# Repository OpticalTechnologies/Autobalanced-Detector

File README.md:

# Autobalanced-Detector
Full KiCAD design and production files of a self designed autobalanced detector for SRS microscopy. 

The autobalanced detector consists of three parts: 
1. Two of the same detectors (SRSDetV5_24V) to detect the signal and reference beam.
2. The autobalancer module.
3. The PID controller, which is designed as a seperate PCB controlled by an MCU. The MCU also controlls logic circuitry on the autobalancer module.

The SRSDetV5 is optimized for use with a 20MHz modulation frequency and incorperates several filters to supress the repetition rate of a 40MHz pulsed laser and its harmonics. 

Firmware for the PID MCU and instructions on how to upload the firmware to the MCU will follow.

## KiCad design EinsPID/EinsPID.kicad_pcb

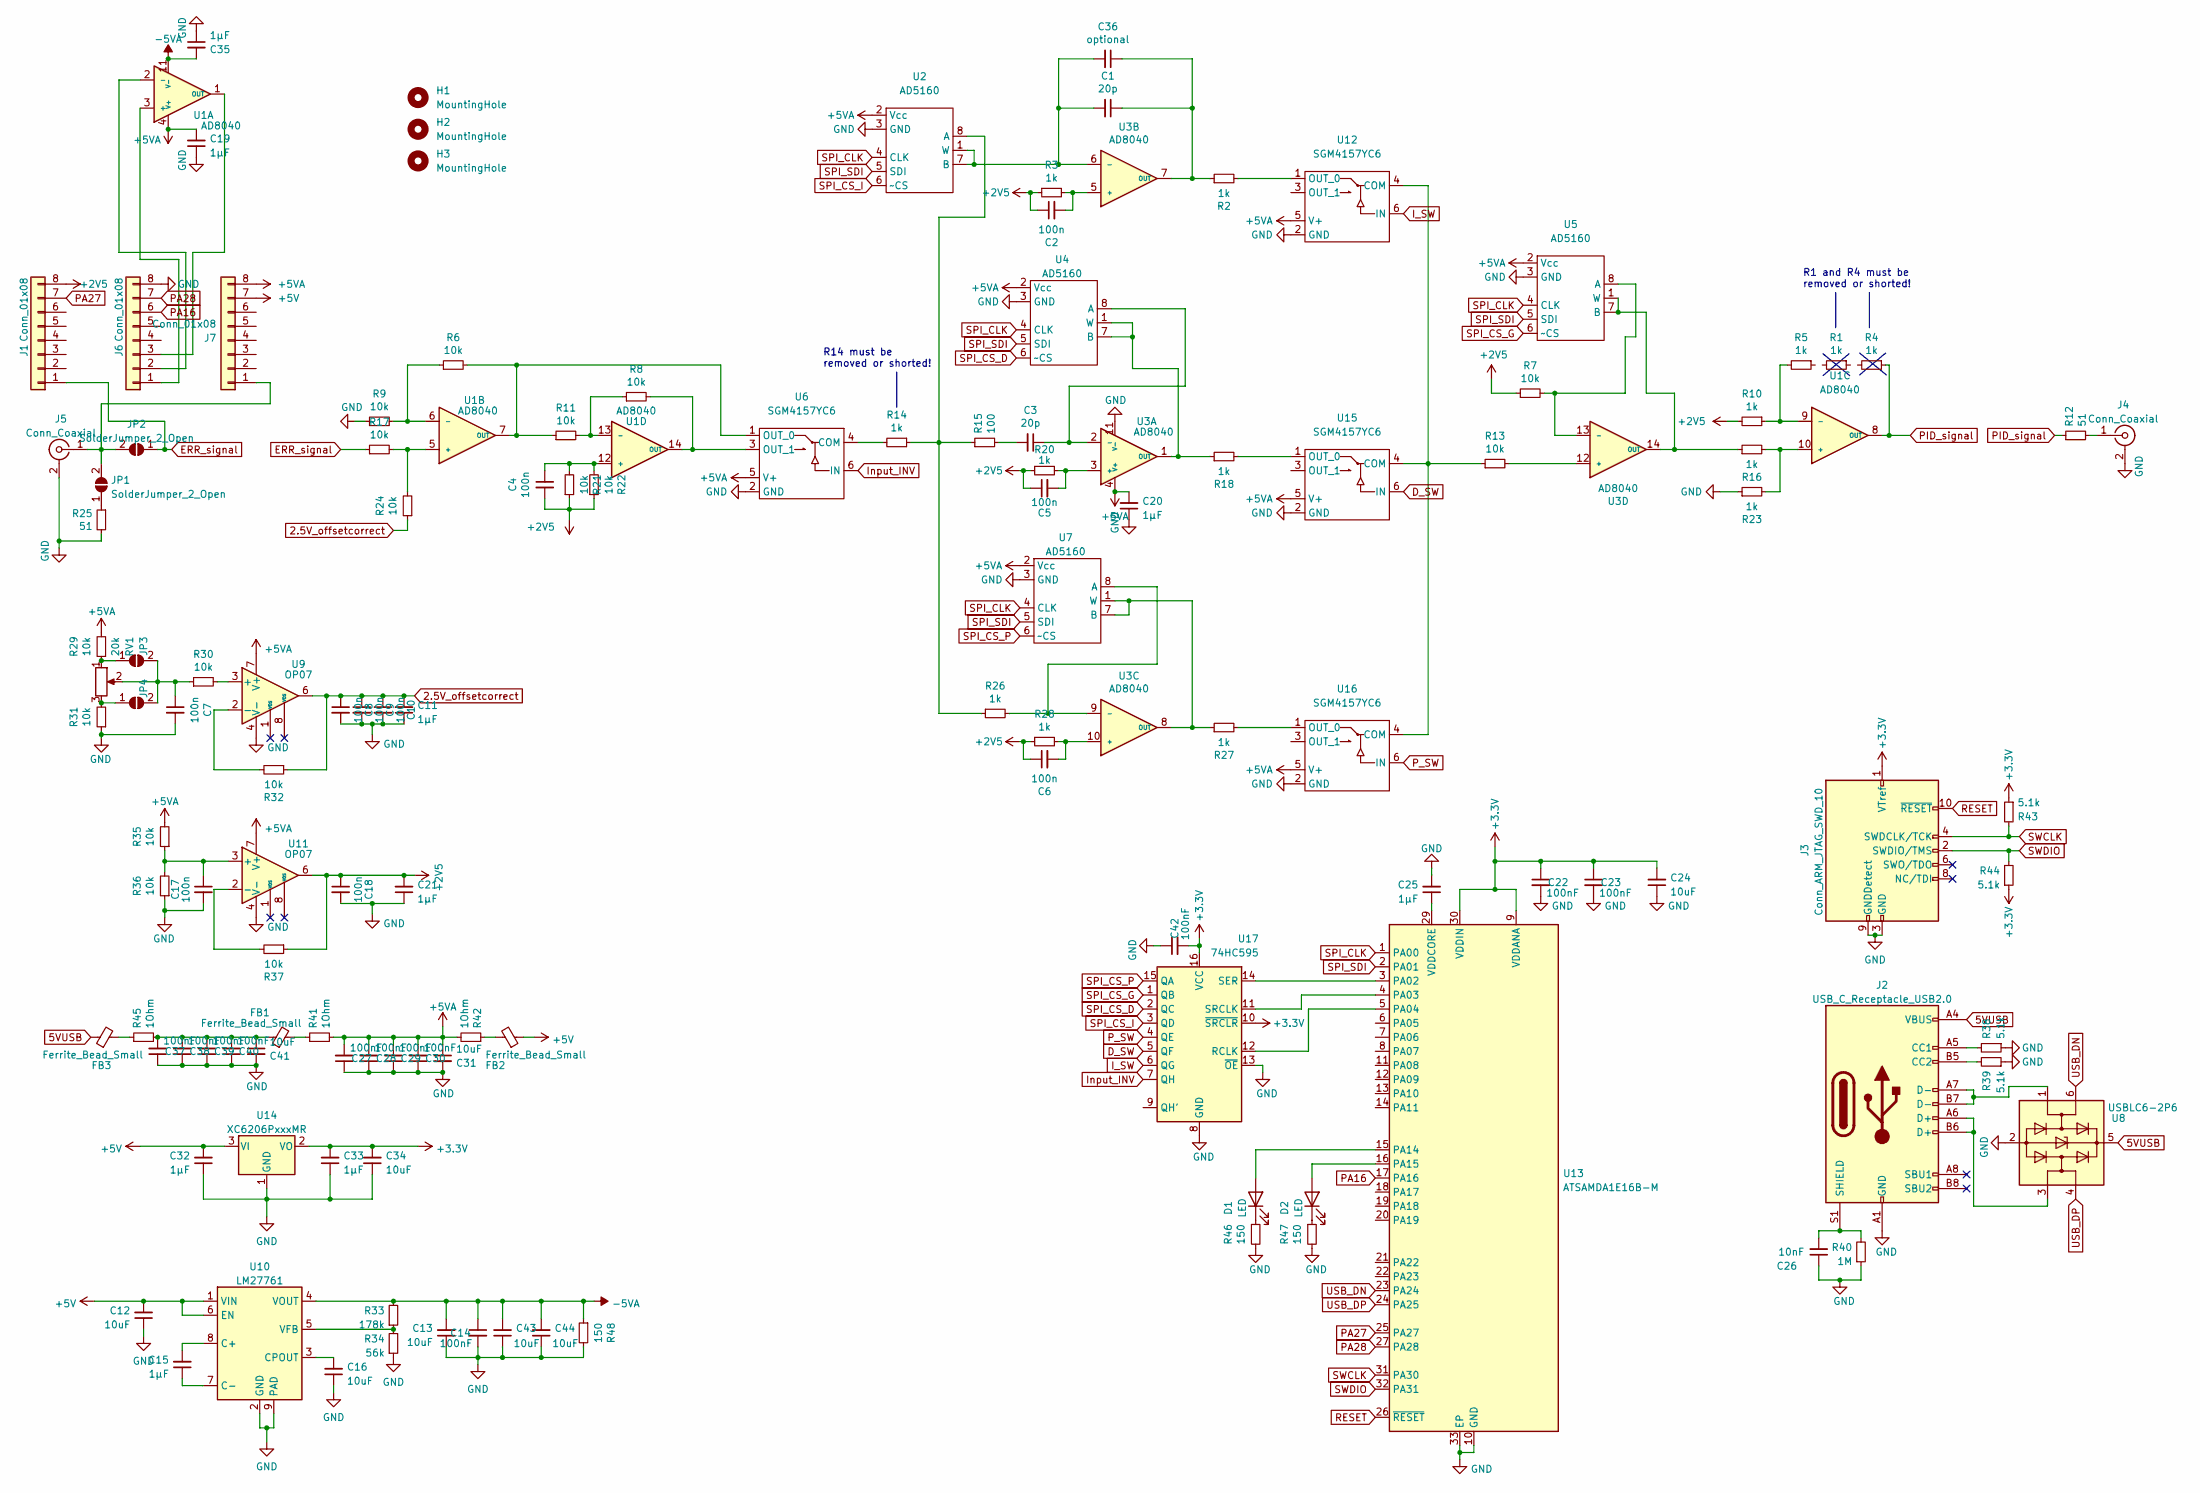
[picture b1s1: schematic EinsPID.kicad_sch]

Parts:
C1, C3: 20p; C_0402_1005Metric; LCSC C1554
C2, C4, C5, C6, C7, C8, C9, C10, C17, C18: 100n; C_0402_1005Metric; LCSC C1525
C11, C15, C19, C20, C21, C25, C32, C33, C35: 1µF; C_0402_1005Metric; LCSC C52923
C12, C13, C16, C24, C31, C34, C41, C43, C44: 10uF; C_0402_1005Metric; LCSC C386033
C14, C22, C23, C27, C28, C29, C30, C37, C38, C39, C40, C42: 100nF; C_0402_1005Metric; LCSC C307331
C26: 10nF; C_0402_1005Metric; LCSC C15195
C36: optional; C_Rect_L4.0mm_W2.5mm_P2.50mm
D1, D2: LED; LED_0603_1608Metric; LCSC C2286
FB1, FB2, FB3: Ferrite_Bead_Small; L_0603_1608Metric; LCSC C1002
H1: MountingHole; Logo_AGFallnich_text
H2: MountingHole; Logo_OptischeTechnologien
H3: MountingHole; Logo_WWU
J1, J6, J7: Conn_01x08; PinHeader_1x08_P2.54mm_Vertical
J2: USB_C_Receptacle_USB2.0; USB_C_Receptacle_XKB_U262-16XN-4BVC11; LCSC C709357
J3: Conn_ARM_JTAG_SWD_10; PinHeader_2x05_P1.27mm_Vertical_SMD
J4, J5: Conn_Coaxial; SMA_edge_pinholes
JP1, JP2, JP3, JP4: SolderJumper_2_Open; 0603_solderbridge
R1, R2, R3, R4, R5, R10, R14, R16, R18, R20, R23, R26, R27, R28: 1k; R_0402_1005Metric; LCSC C11702
R6, R7, R8, R9, R11, R13, R17, R21, R22, R24, R29, R30, R31, R32, R35, R36, R37: 10k; R_0402_1005Metric; LCSC C25744
R12, R25: 51; R_0402_1005Metric; LCSC C25125
R15: 100; R_0402_1005Metric; LCSC C25076
R33: 178k; R_0402_1005Metric; LCSC C26995
R34: 56k; R_0402_1005Metric; LCSC C25796
R38, R39, R43, R44: 5.1k; R_0402_1005Metric; LCSC C25905
R40: 1M; R_0402_1005Metric; LCSC C26083
R41, R42, R45: 1Ohm; R_0402_1005Metric; LCSC C25086
R46, R47, R48: 150; R_0402_1005Metric; LCSC C25082
RV1: 20k; Potentiometer_Bourns_3296W_Vertical
U1, U3: AD8040; SOIC-14_3.9x8.7mm_P1.27mm
U2, U4, U5, U7: AD5160; SOT-23-8; LCSC C40097
U6, U12, U15, U16: SGM4157YC6; SC-60; LCSC C124895
U8: USBLC6-2P6; SOT-666; LCSC C2827693
U9, U11: OP07; SOIC-8_3.9x4.9mm_P1.27mm; LCSC C7433
U10: LM27761; WSON-8-1EP_2x2mm_P0.5mm_EP0.9x1.6mm; LCSC C129351
U13: ATSAMDA1E16B-M; QFN-32-1EP_5x5mm_P0.5mm_EP3.6x3.6mm
U14: XC6206PxxxMR; SOT-23; LCSC C5446
U17: 74HC595; SOIC-16_3.9x9.9mm_P1.27mm; LCSC C5947

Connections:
2.5V_offsetcorrect: C8.1, C9.1, C10.1, C11.2, R24.1, R32.1, U9.6
5VUSB: FB3.1, J2.A4 (VBUS), J2.A9 (VBUS), J2.B4 (VBUS), J2.B9 (VBUS), U8.5 (VBUS)
+2V5: C2.1, C4.2, C5.1, C6.1, C18.1, C21.2, J1.8, R3.1, R7.1, R10.2, R20.1, R21.1, R22.1, R28.1, R37.1, U11.6
+3V3: C22.1, C23.1, C24.2, C33.2, C34.2, C42.2, J3.1 (VTref), R43.1, R44.1, U13.9 (VDDANA), U13.30 (VDDIN), U14.2 (VO), U17.10 (~SRCLR), U17.16 (VCC)
+5V: C12.2, C32.2, FB2.1, J7.7, U10.1 (VIN), U10.6 (EN), U14.3 (VI)
+5VA: C19.2, C20.2, C27.2, C28.2, C29.2, C30.2, C31.1, J7.8, R29.2, R35.2, R41.2, R42.2, U1.4 (V+), U2.2 (Vcc), U3.4 (V+), U4.2 (Vcc), U5.2 (Vcc), U6.5 (V+), U7.2 (Vcc), U9.7 (V+), U11.7 (V+), U12.5 (V+), U15.5 (V+), U16.5 (V+)
-5VA: C13.2, C14.1, C35.2, C43.2, C44.2, R33.2, R48.1, U1.11 (V-), U10.4 (VOUT)
D_SW: U15.6 (IN), U17.5 (QF)
ERR_signal: J1.1, JP2.1 (A), R17.1
GND: C7.2, C8.2, C9.2, C10.2, C11.1, C12.1, C13.1, C14.2, C16.1, C17.2, C18.2, C19.1, C20.1, C21.1, C22.2, C23.2, C24.1, C25.2, C26.1, C27.1, C28.1, C29.1, C30.1, C31.2, C32.1, C33.1, C34.1, C35.1, C37.1, C38.1, C39.1, C40.1, C41.2, C42.1, C43.1, C44.1, J2.A1 (GND), J2.A12 (GND), J2.B1 (GND), J2.B12 (GND), J3.3 (GND), J3.5 (GND), J3.9 (GNDDetect), J4.2 (Ext), J5.2 (Ext), J6.8, R9.1, R23.1, R25.2, R31.1, R34.1, R36.1, R38.1, R39.1, R40.1, R46.2, R47.2, R48.2, U2.3 (GND), U3.11 (V-), U4.3 (GND), U5.3 (GND), U6.2 (GND), U7.3 (GND), U8.2 (GND), U9.4 (V-), U10.2 (GND), U10.9 (PAD), U11.4 (V-), U12.2 (GND), U13.10 (GND), U13.28 (GND), U13.33 (EP), U14.1 (GND), U15.2 (GND), U16.2 (GND), U17.8 (GND), U17.13 (~OE)
I_SW: U12.6 (IN), U17.6 (QG)
Input_INV: U6.6 (IN), U17.7 (QH)
unnamed: C1.1, C36.1, R2.1, U3.7 (OUT)
unnamed: C1.2, C36.2, U2.1 (W), U2.7 (B), U3.6 (-)
unnamed: C2.2, R3.2, U3.5 (+)
unnamed: C3.1, U3.2 (-), U4.8 (A)
unnamed: C3.2, R15.2
unnamed: C4.1, R21.2, R22.2, U1.12 (+)
unnamed: C5.2, R20.2, U3.3 (+)
unnamed: C6.2, R28.2, U3.10 (+)
unnamed: C7.1, JP3.2 (B), JP4.2 (B), R30.1, RV1.2
unnamed: C15.1, U10.7 (C-)
unnamed: C15.2, U10.8 (C+)
unnamed: C16.2, U10.3 (CPOUT)
unnamed: C17.1, R35.1, R36.2, U11.3 (+)
unnamed: C25.1, U13.29 (VDDCORE)
unnamed: C26.2, J2.S1 (SHIELD), R40.2
unnamed: C37.2, C38.2, C39.2, C40.2, C41.1, FB1.1, R45.2
unnamed: D1.1 (K), R46.1
unnamed: D1.2 (A), U13.15 (PA14)
unnamed: D2.1 (K), R47.1
unnamed: D2.2 (A), U13.16 (PA15)
unnamed: FB1.2, R41.1
unnamed: FB2.2, R42.1
unnamed: FB3.2, R45.1
unnamed: J2.A5 (CC1), R38.2
unnamed: J2.A6 (D+), J2.B6 (D+), U8.3 (I/O2)
unnamed: J2.A7 (D-), J2.B7 (D-), U8.1 (I/O1)
unnamed: J2.B5 (CC2), R39.2
unnamed: J4.1 (In), R12.2
unnamed: J5.1 (In), J7.1, JP1.2 (B), JP2.2 (B)
unnamed: J6.1, U1.3 (+)
unnamed: J6.2, U1.2 (-)
unnamed: J6.3, U1.1 (OUT)
unnamed: JP1.1 (A), R25.1
unnamed: JP3.1 (A), R29.1, RV1.1
unnamed: JP4.1 (A), R31.2, RV1.3
unnamed: R1.1, R4.2
unnamed: R1.2, R5.1
unnamed: R2.2, U12.1 (OUT_0)
unnamed: R6.1, R9.2, U1.6 (-)
unnamed: R7.2, U3.13 (-), U5.8 (A)
unnamed: R8.2, U1.14 (OUT), U6.3 (OUT_1)
unnamed: R5.2, R10.1, U1.9 (-)
unnamed: R6.2, R11.1, U1.7 (OUT), U6.1 (OUT_0)
unnamed: R8.1, R11.2, U1.13 (-)
unnamed: R13.1, U12.4 (COM), U15.4 (COM), U16.4 (COM)
unnamed: R13.2, U3.12 (+)
unnamed: R14.1, R15.1, R26.1, U2.8 (A)
unnamed: R16.1, U3.14 (OUT), U5.1 (W), U5.7 (B)
unnamed: R16.2, R23.2, U1.10 (+)
unnamed: R17.2, R24.2, U1.5 (+)
unnamed: R18.1, U3.1 (OUT), U4.1 (W), U4.7 (B)
unnamed: R18.2, U15.1 (OUT_0)
unnamed: R26.2, U3.9 (-), U7.8 (A)
unnamed: R27.1, U3.8 (OUT), U7.1 (W), U7.7 (B)
unnamed: R27.2, U16.1 (OUT_0)
unnamed: R30.2, U9.3 (+)
unnamed: R32.2, U9.2 (-)
unnamed: R33.1, R34.2, U10.5 (VFB)
unnamed: R37.2, U11.2 (-)
unnamed: R14.2, U6.4 (COM)
unnamed: U13.3 (PA02), U17.14 (SER)
unnamed: U13.4 (PA03), U17.11 (SRCLK)
unnamed: U13.5 (PA04), U17.12 (RCLK)
PA16: J6.6, U13.17 (PA16)
PA27: J1.7, U13.25 (PA27)
PA28: J6.7, U13.27 (PA28)
PID_signal: R4.1, R12.1, U1.8 (OUT)
P_SW: U16.6 (IN), U17.4 (QE)
RESET: J3.10 (~RESET), U13.26 (~RESET)
SPI_CLK: U2.4 (CLK), U4.4 (CLK), U5.4 (CLK), U7.4 (CLK), U13.1 (PA00)
SPI_CS_D: U4.6 (~CS), U17.2 (QC)
SPI_CS_G: U5.6 (~CS), U17.1 (QB)
SPI_CS_I: U2.6 (~CS), U17.3 (QD)
SPI_CS_P: U7.6 (~CS), U17.15 (QA)
SPI_SDI: U2.5 (SDI), U4.5 (SDI), U5.5 (SDI), U7.5 (SDI), U13.2 (PA01)
SWCLK: J3.4 (SWDCLK/TCK), R43.2, U13.31 (PA30)
SWDIO: J3.2 (SWDIO/TMS), R44.2, U13.32 (PA31)
USB_DN: U8.6 (I/O1), U13.23 (PA24)
USB_DP: U8.4 (I/O2), U13.24 (PA25)

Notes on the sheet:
R14 must be removed or shorted!
R1 and R4 must be removed or shorted!

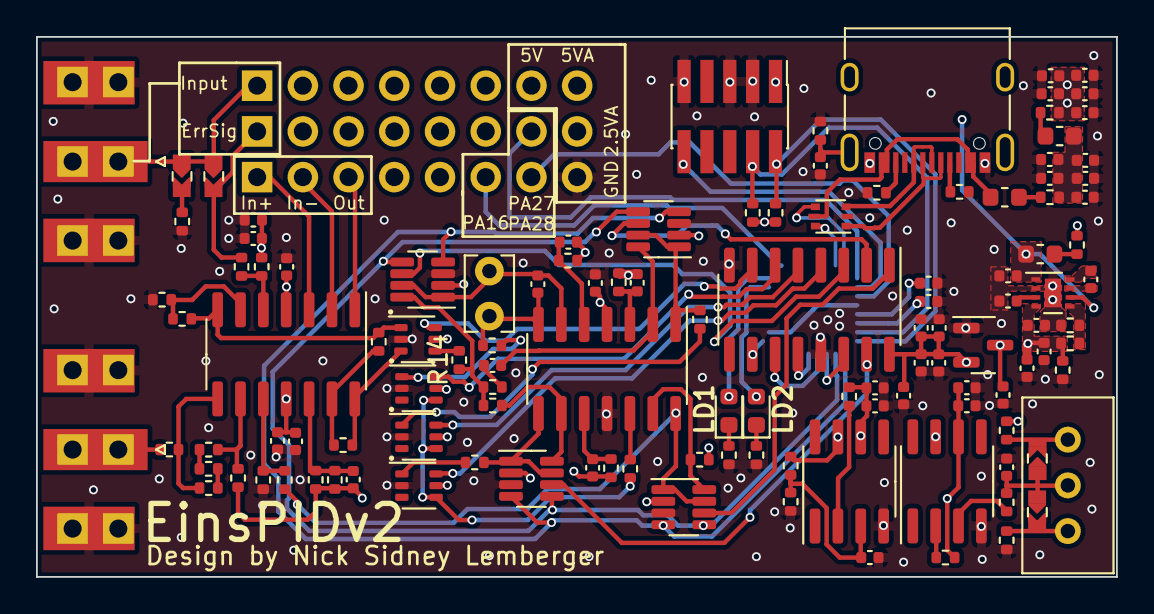
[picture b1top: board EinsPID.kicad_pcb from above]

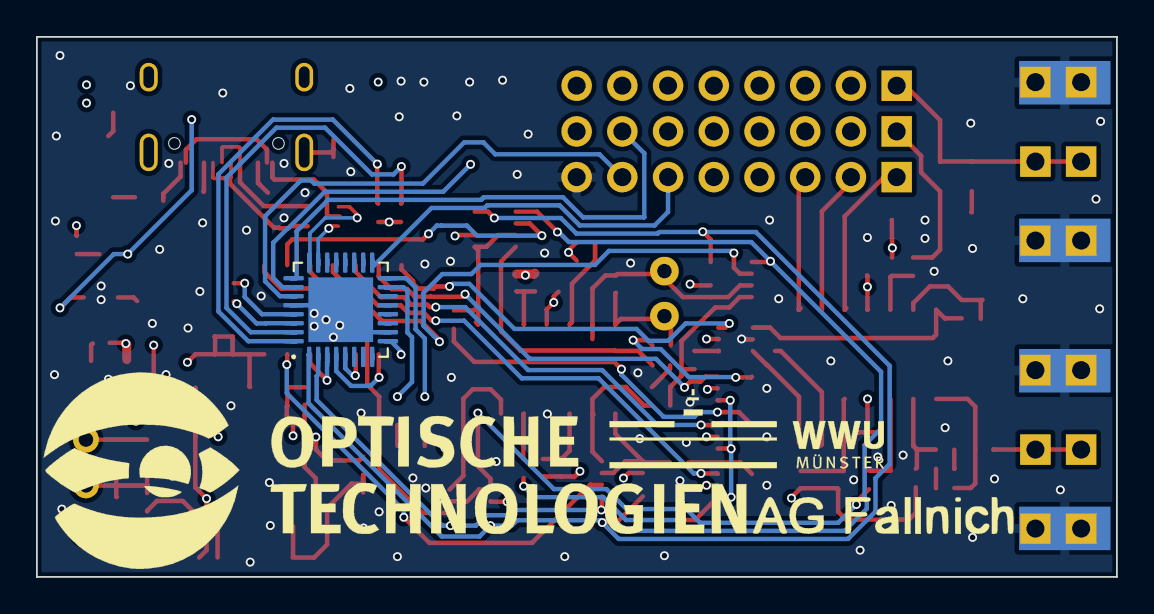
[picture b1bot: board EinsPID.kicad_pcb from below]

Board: 4 copper layers, 60.0 x 30.0 mm, 128 parts (4 on the bottom side), 91 nets.

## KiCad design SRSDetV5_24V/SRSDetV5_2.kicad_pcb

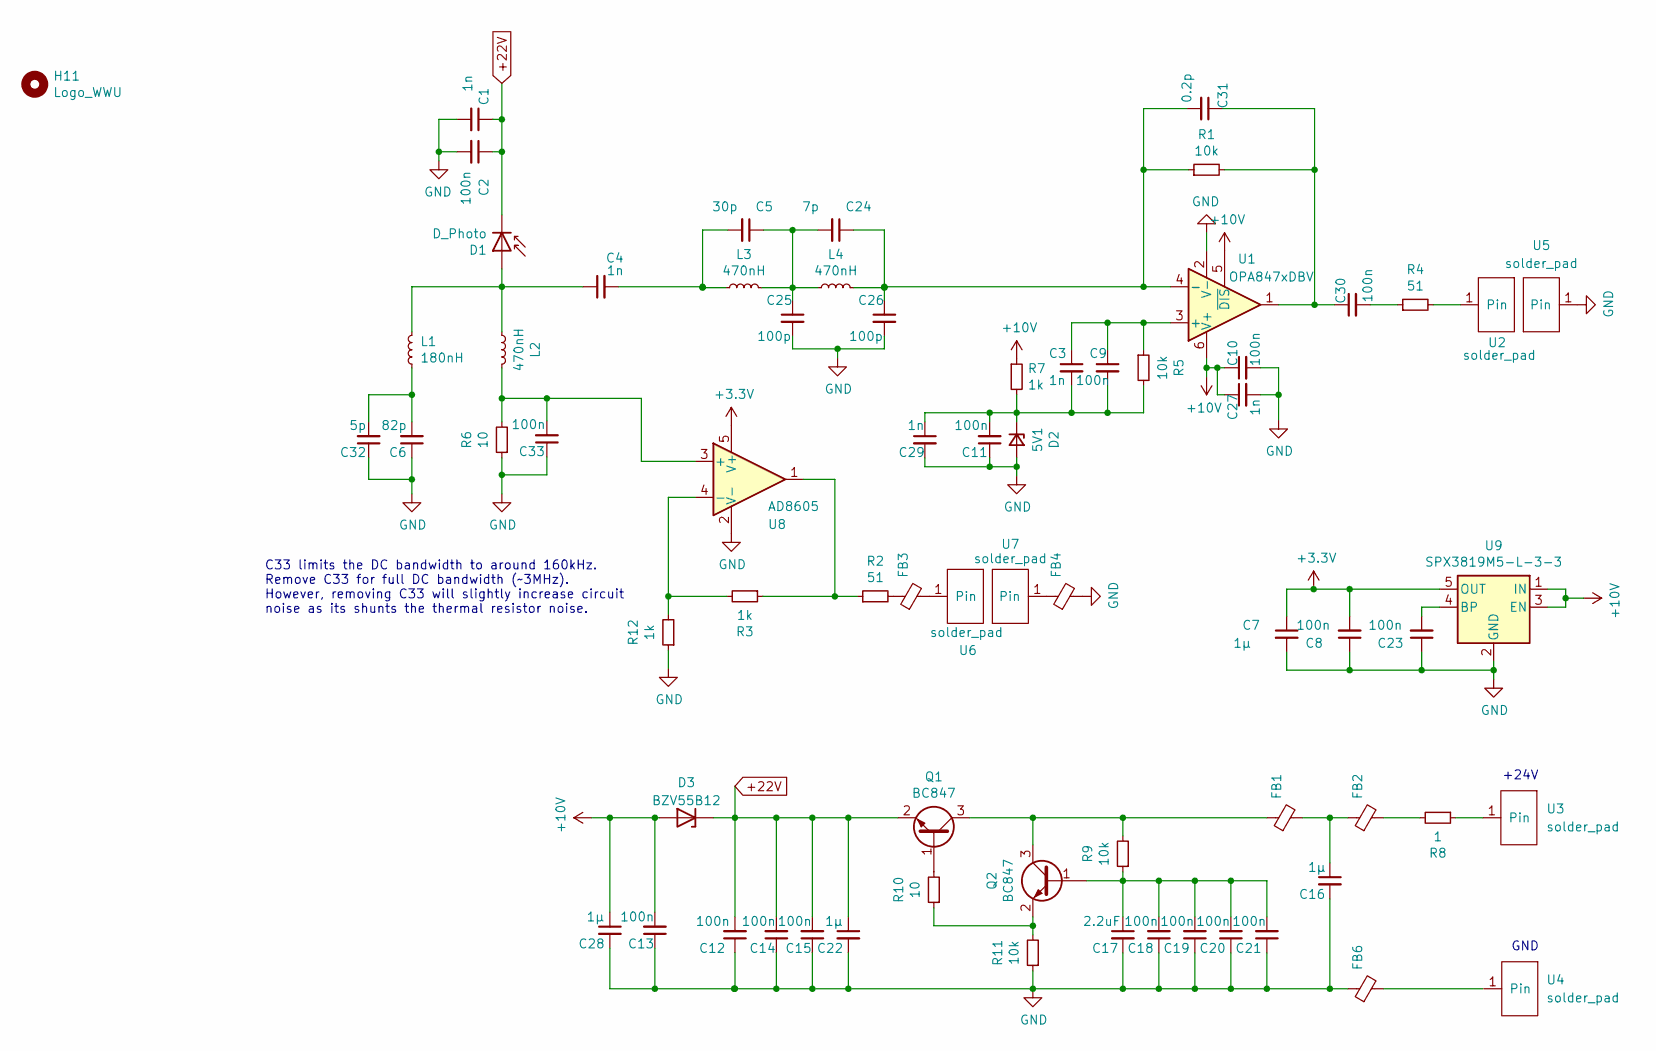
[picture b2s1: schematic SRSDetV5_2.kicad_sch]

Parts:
C1, C3, C4, C27, C29: 1n; C_0402_1005Metric; LCSC C1523
C2, C8, C9, C10, C11, C12, C13, C14, C15, C18, C19, C20, C21, C23, C30, C33: 100n; C_0402_1005Metric; LCSC C1525
C5: 30p; C_0402_1005Metric; LCSC C1570
C6: 82p; C_0402_1005Metric; LCSC C13532
C7, C16, C22, C28: 1µ; C_0402_1005Metric; LCSC C52923
C17: 2.2uF; C_1206_3216Metric; LCSC C50254
C24: 7p; C_0402_1005Metric; LCSC C114403
C25, C26: 100p; C_0402_1005Metric; LCSC C1546
C31: 0.2p; C_0402_1005Metric; LCSC C161339
C32: 5p; C_0402_1005Metric; LCSC C880630
D1: D_Photo; S3590-xx
D2: 5V1; D_SOD-323; LCSC C173436
D3: BZV55B12; D_MiniMELF; LCSC C545385
FB1, FB2, FB3, FB4, FB6: Ferrite_Bead_Small; L_0603_1608Metric; LCSC C1002
H11: Logo_WWU
L1: 180nH; L_0805_2012Metric; LCSC C251836
L2, L3, L4: 470nH; L_0603_1608Metric; LCSC C127457
Q1, Q2: BC847; SOT-23; LCSC C8664
R1: 10k; R_0402_1005Metric; LCSC C84351
R2, R4: 51; R_0402_1005Metric; LCSC C25125
R3, R7, R12: 1k; R_0402_1005Metric; LCSC C328418
R5, R9, R11: 10k; R_0402_1005Metric; LCSC C25744
R6: 10; R_0402_1005Metric; LCSC C319916
R8: 1; R_0402_1005Metric; LCSC C25086
R10: 10; R_0402_1005Metric; LCSC C25077
U1: OPA847xDBV; SOT-23-6; LCSC C160422
U2, U3, U4, U5, U6, U7: solder_pad
U8: AD8605; SOT-23-5; LCSC C9641
U9: SPX3819M5-L-3-3; SOT-23-5; LCSC C9055

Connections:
+3V3: C7.1, C8.2, U8.5 (V+), U9.5 (OUT)
+10V: C10.1, C13.2, C27.1, C28.1, D3.2 (A), R7.1, U1.5 (~DIS), U1.6 (V+), U9.1 (IN), U9.3 (EN)
+22V: C1.1, C2.1, C12.2, C14.2, C15.2, C22.1, D1.1 (K), D3.1 (K), Q1.2 (E)
GND: C1.2, C2.2, C6.1, C7.2, C8.1, C10.2, C11.1, C12.1, C13.1, C14.1, C15.1, C16.2, C17.2, C18.1, C19.1, C20.1, C21.1, C22.2, C23.1, C25.2, C26.2, C27.2, C28.2, C29.2, C32.1, C33.1, D2.2 (A), FB4.2, FB6.1, R6.1, R11.1, R12.1, U1.2 (V-), U5.1, U8.2 (V-), U9.2 (GND)
unnamed: C3.1, C9.1, R5.1, U1.3 (+)
unnamed: C4.1, D1.2 (A), L1.2, L2.1
unnamed: C4.2, C5.2, L3.1
unnamed: C3.2, C9.2, C11.2, C29.1, D2.1 (K), R5.2, R7.2
unnamed: C16.1, FB1.2, FB2.1
unnamed: C17.1, C18.2, C19.2, C20.2, C21.2, Q2.1 (B), R9.1
unnamed: C23.2, U9.4 (BP)
unnamed: C24.1, C26.1, C31.2, L4.2, R1.1, U1.4 (-)
unnamed: C5.1, C24.2, C25.1, L3.2, L4.1
unnamed: C30.1, C31.1, R1.2, U1.1
unnamed: C30.2, R4.1
unnamed: C6.2, C32.2, L1.1
unnamed: C33.2, L2.2, R6.2, U8.3 (+)
unnamed: FB1.1, Q1.3 (C), Q2.3 (C), R9.2
unnamed: FB2.2, R8.2
unnamed: FB3.1, R2.2
unnamed: FB3.2, U6.1
unnamed: FB4.1, U7.1
unnamed: Q1.1 (B), R10.2
unnamed: Q2.2 (E), R10.1, R11.2
unnamed: R2.1, R3.1, U8.1
unnamed: R4.2, U2.1
unnamed: R8.1, U3.1
unnamed: R3.2, R12.2, U8.4 (-)

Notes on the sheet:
+24V
C33 limits the DC bandwidth to around 160kHz. Remove C33 for full DC bandwidth (~3MHz). However, removing C33 will slightly increase circuit noise as its shunts the thermal resistor noise.
GND

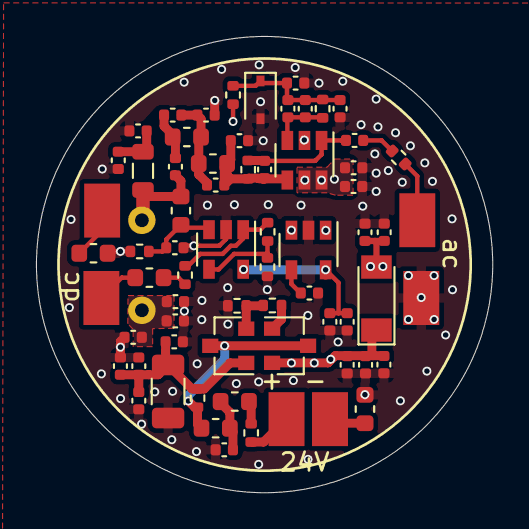
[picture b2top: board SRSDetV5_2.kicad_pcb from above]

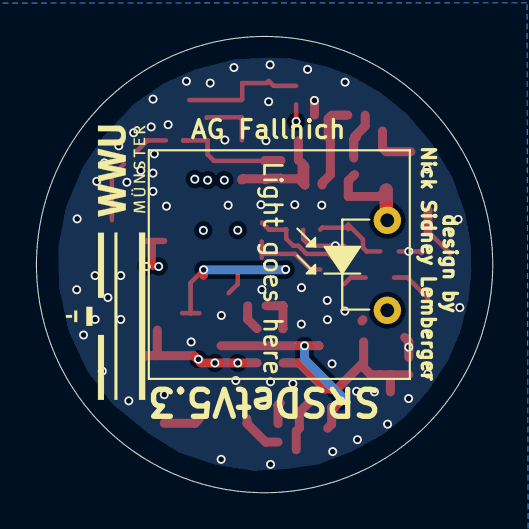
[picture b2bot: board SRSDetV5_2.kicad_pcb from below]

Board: 4 copper layers, 25.3 x 25.3 mm, 69 parts (2 on the bottom side), 28 nets.

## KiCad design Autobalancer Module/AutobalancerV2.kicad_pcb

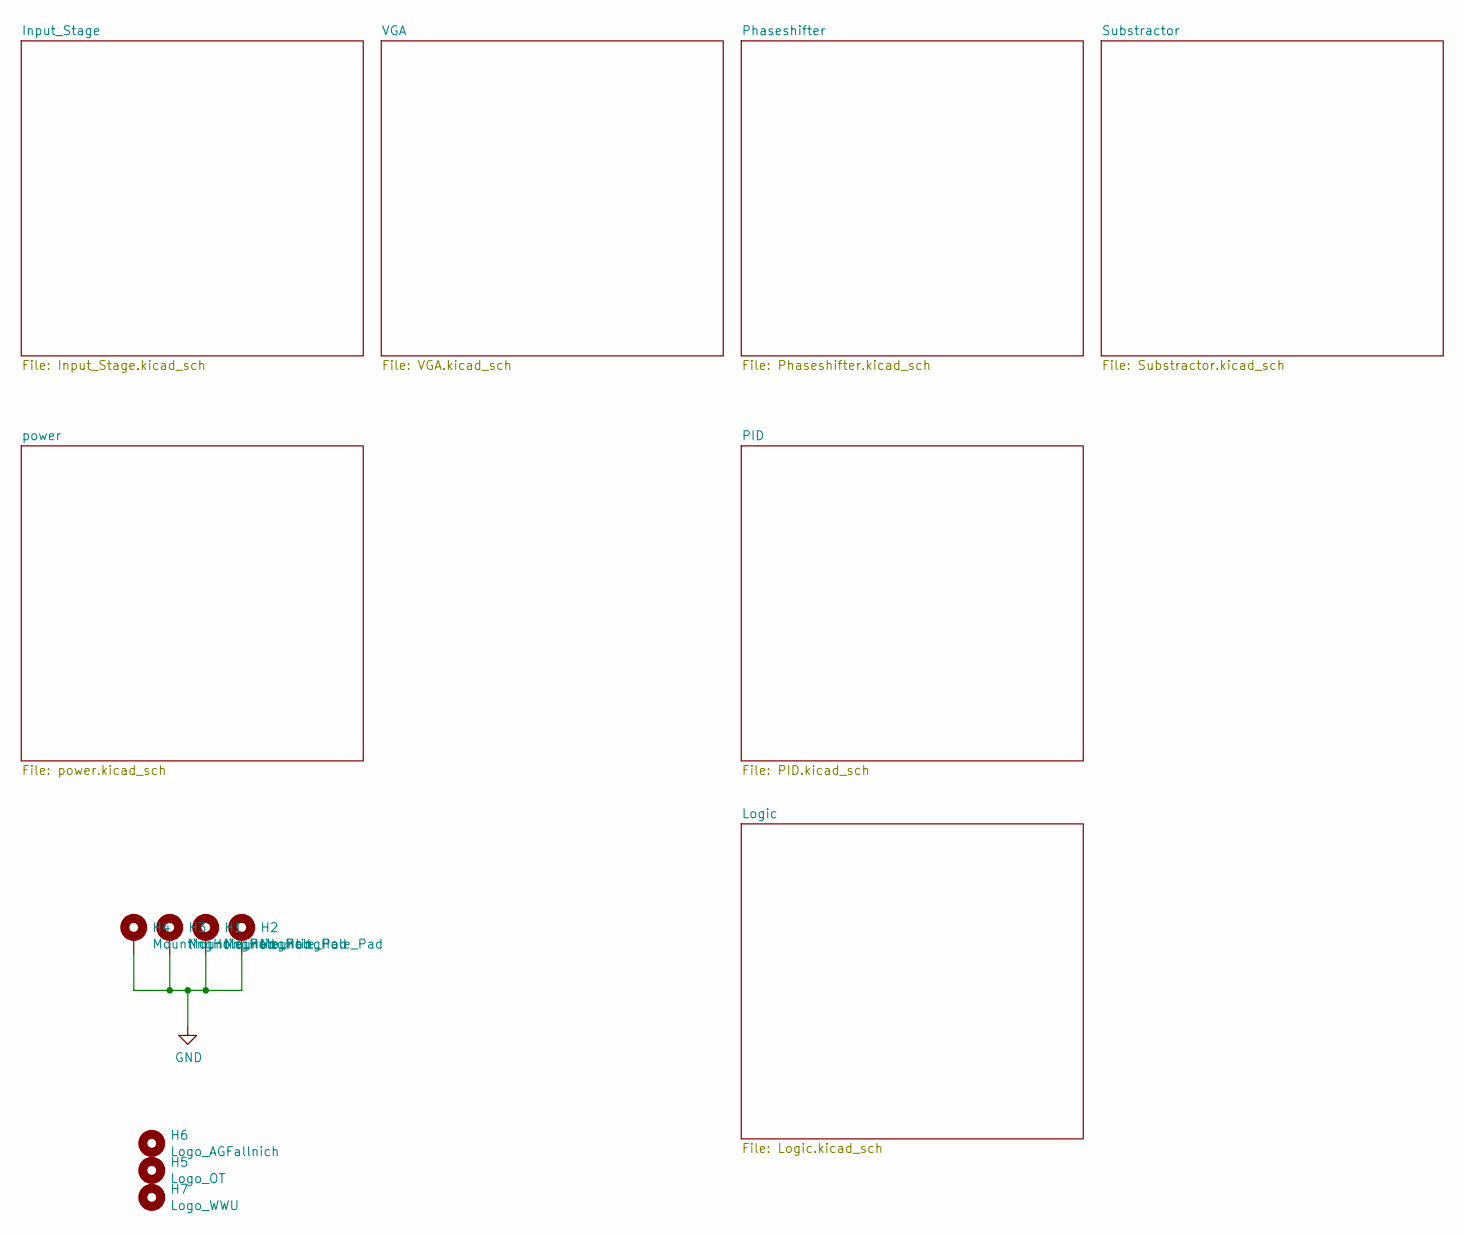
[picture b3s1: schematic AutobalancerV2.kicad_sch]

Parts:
H1, H2, H3, H4: MountingHole_Pad; MountingHole_3.2mm_M3_Pad_Via
H5: Logo_OT; Logo_OptischeTechnologien
H6: Logo_AGFallnich; Logo_AGFallnich_text
H7: Logo_WWU

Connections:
GND: H1.1, H2.1, H3.1, H4.1; also elsewhere on the board

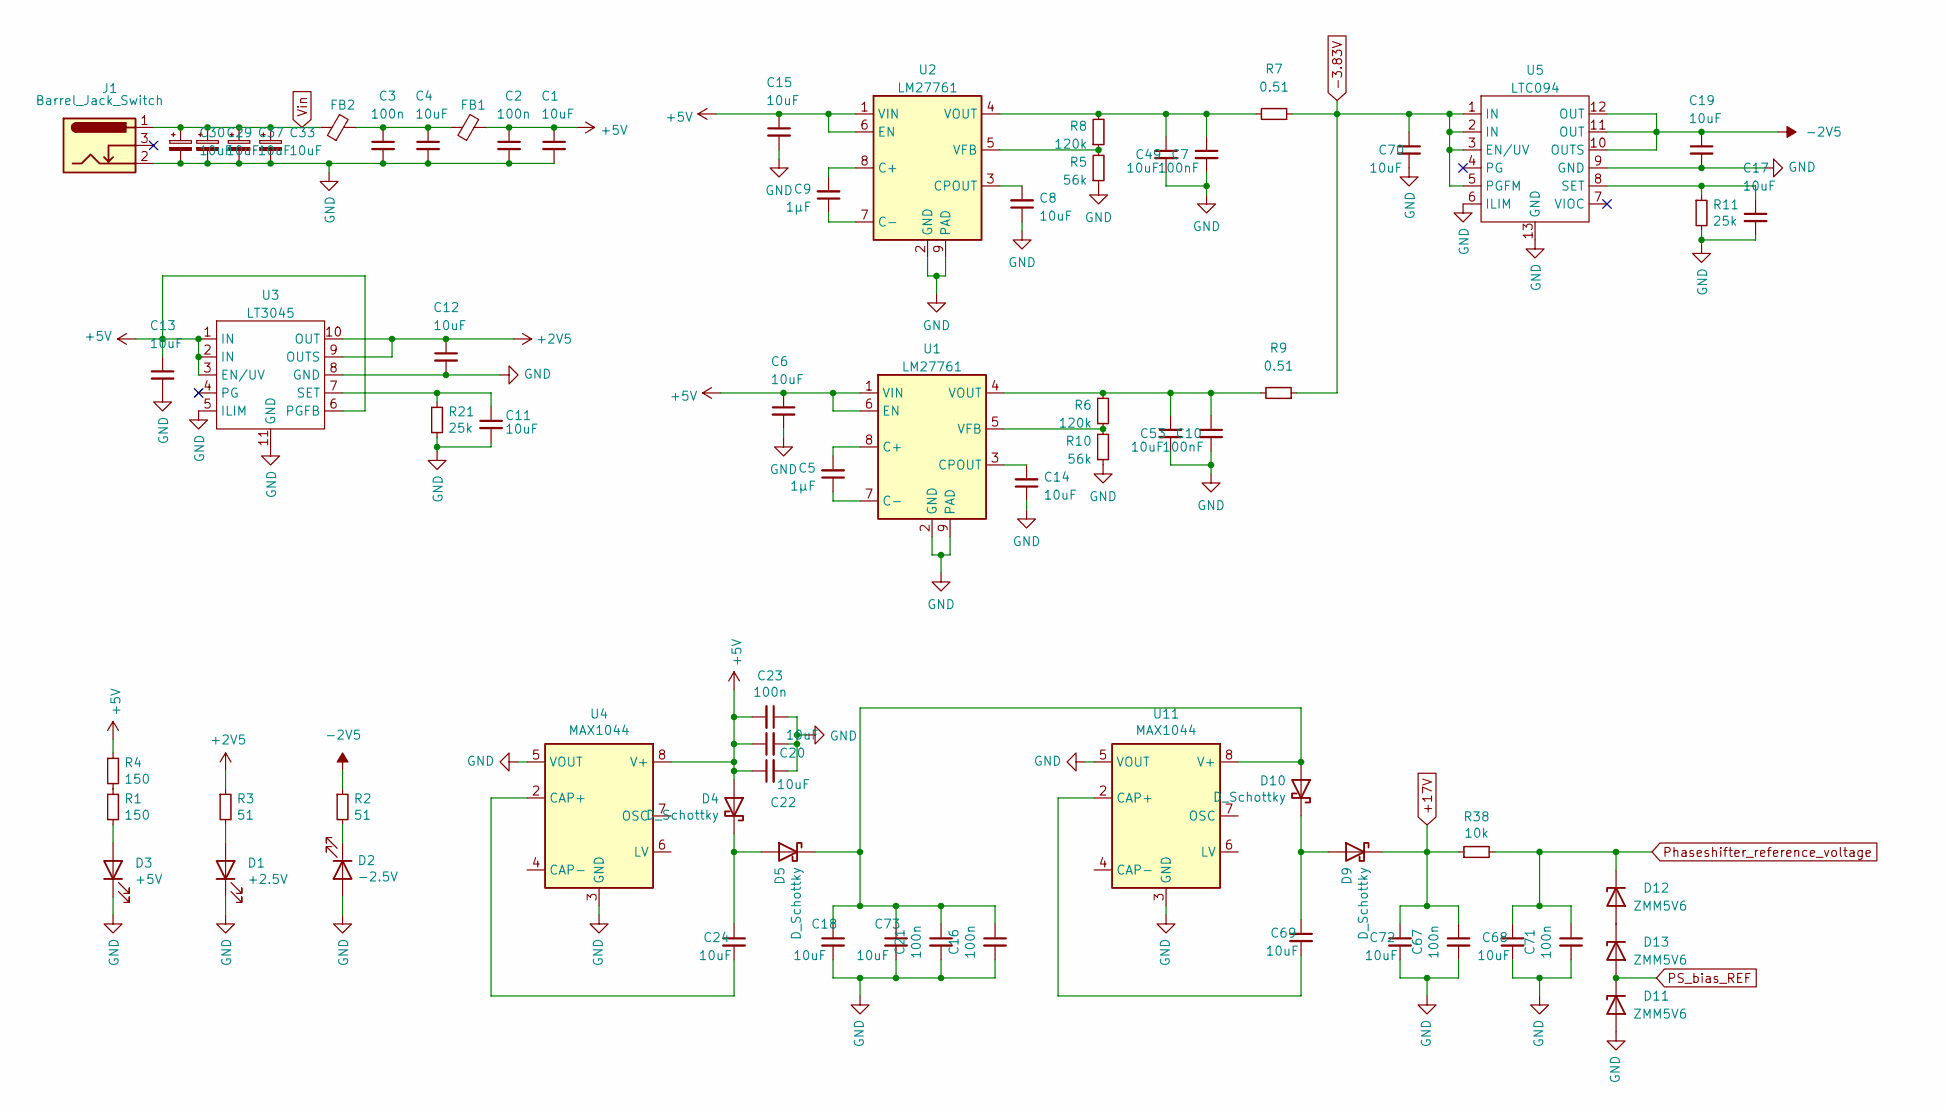
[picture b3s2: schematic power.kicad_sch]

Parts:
C1, C4, C6, C11, C12, C13, C15, C17, C18, C19, C20, C22, C24, C49, C53, C68, C69, C70, C72, C73: 10uF; C_1206_3216Metric; LCSC C13585
C2, C3, C16, C21, C23, C67, C71: 100n; C_0402_1005Metric; LCSC C1525
C5, C9: 1µF; C_0402_1005Metric; LCSC C52923
C7, C10: 100nF; C_0402_1005Metric; LCSC C307331
C8, C14: 10uF; C_0402_1005Metric; LCSC C386033
C29, C30, C33, C37: 10uF; CP_EIA-3216-18_Kemet-A; LCSC C7171
D1: +2.5V; LED_0603_1608Metric; LCSC C2286
D2: -2.5V; LED_0603_1608Metric; LCSC C2286
D3: +5V; LED_0603_1608Metric; LCSC C2286
D4, D5, D9, D10: D_Schottky; D_SOD-123; LCSC C8598
D11, D12, D13: ZMM5V6; D_MiniMELF; LCSC C8062
FB1, FB2: Ferrite_Bead_Small; L_0805_2012Metric; LCSC C74323
J1: Barrel_Jack_Switch; BarrelJack_CUI_PJ-102AH_Horizontal_with3D
R1, R4: 150; R_0402_1005Metric; LCSC C25082
R2, R3: 51; R_0402_1005Metric; LCSC C25125
R5, R10: 56k; R_0402_1005Metric; LCSC C25796
R6, R8: 120k; R_0402_1005Metric; LCSC C25750
R7, R9: 0.51; R_0402_1005Metric; LCSC C423100
R11, R21: 25k; R_0805_2012Metric; LCSC C316201
R38: 10k; R_0402_1005Metric; LCSC C25744
U1, U2: LM27761; WSON-8-1EP_2x2mm_P0.5mm_EP0.9x1.6mm; LCSC C129351
U3: LT3045; DFN-10-1EP_3x3mm_P0.5mm_EP1.65x2.38mm; LCSC C666574
U4, U11: MAX1044; SOIC-8_3.9x4.9mm_P1.27mm; LCSC C140450
U5: LTC094; DFN-12-1EP_3x3mm_P0.45mm_EP1.66x2.38mm

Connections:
+2V5: C12.1, R3.1, U3.9 (OUTS), U3.10 (OUT); also elsewhere on the board
+5V: C1.1, C2.1, C6.1, C13.1, C15.1, C20.1, C22.1, C23.2, D4.2 (A), FB1.2, R4.1, U1.1 (VIN), U1.6 (EN), U2.1 (VIN), U2.6 (EN), U3.1 (IN), U3.2 (IN), U3.3 (EN/UV), U3.6 (PGFB), U4.8 (V+); also elsewhere on the board
+17V: C67.1, C72.1, D9.1 (K), R38.1; also elsewhere on the board
-2V5: C19.1, R2.1, U5.10 (OUTS), U5.11 (OUT), U5.12 (OUT); also elsewhere on the board
-3.83V: C70.1, R7.1, R9.1, U5.1 (IN), U5.2 (IN), U5.3 (EN/UV), U5.5 (PGFM)
GND: C1.2, C2.2, C3.2, C4.2, C6.2, C7.2, C8.1, C10.2, C11.2, C12.2, C13.2, C14.1, C15.2, C16.2, C17.2, C18.2, C19.2, C20.2, C21.2, C22.2, C23.1, C29.2, C30.2, C33.2, C37.2, C49.2, C53.2, C67.2, C68.2, C70.2, C71.2, C72.2, C73.2, D1.1 (K), D2.2 (A), D3.1 (K), D11.2 (A), J1.2, R5.1, R10.1, R11.2, R21.2, U1.2 (GND), U1.9 (PAD), U2.2 (GND), U2.9 (PAD), U3.5 (ILIM), U3.8 (GND), U3.11 (GND), U4.3 (GND), U4.5 (VOUT), U5.6 (ILIM), U5.9 (GND), U5.13 (GND), U11.3 (GND), U11.5 (VOUT); also elsewhere on the board
unnamed: C3.1, C4.1, FB1.1, FB2.2
unnamed: C5.1, U1.7 (C-)
unnamed: C5.2, U1.8 (C+)
unnamed: C8.2, U2.3 (CPOUT)
unnamed: C9.1, U2.7 (C-)
unnamed: C9.2, U2.8 (C+)
unnamed: C10.1, C53.1, R6.2, R9.2, U1.4 (VOUT)
unnamed: C11.1, R21.1, U3.7 (SET)
unnamed: C14.2, U1.3 (CPOUT)
unnamed: C16.1, C18.1, C21.1, C73.1, D5.1 (K), D10.2 (A), U11.8 (V+)
unnamed: C17.1, R11.1, U5.8 (SET)
unnamed: C24.1, D4.1 (K), D5.2 (A)
unnamed: C24.2, U4.2 (CAP+)
unnamed: C7.1, C49.1, R7.2, R8.2, U2.4 (VOUT)
unnamed: C69.1, D9.2 (A), D10.1 (K)
unnamed: C69.2, U11.2 (CAP+)
unnamed: D1.2 (A), R3.2
unnamed: D2.1 (K), R2.2
unnamed: D3.2 (A), R1.2
unnamed: D12.2 (A), D13.1 (K)
unnamed: R1.1, R4.2
unnamed: R5.2, R8.1, U2.5 (VFB)
unnamed: R6.1, R10.2, U1.5 (VFB)
PS_bias_REF: D11.1 (K), D13.2 (A); also elsewhere on the board
Phaseshifter_reference_voltage: C68.1, C71.1, D12.1 (K), R38.2; also elsewhere on the board
Vin: C29.1, C30.1, C33.1, C37.1, FB2.1, J1.1; also elsewhere on the board
